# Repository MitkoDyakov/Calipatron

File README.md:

# Calipatorn
I design my own digital caliper based on STM32F103C8T6 blue pill.

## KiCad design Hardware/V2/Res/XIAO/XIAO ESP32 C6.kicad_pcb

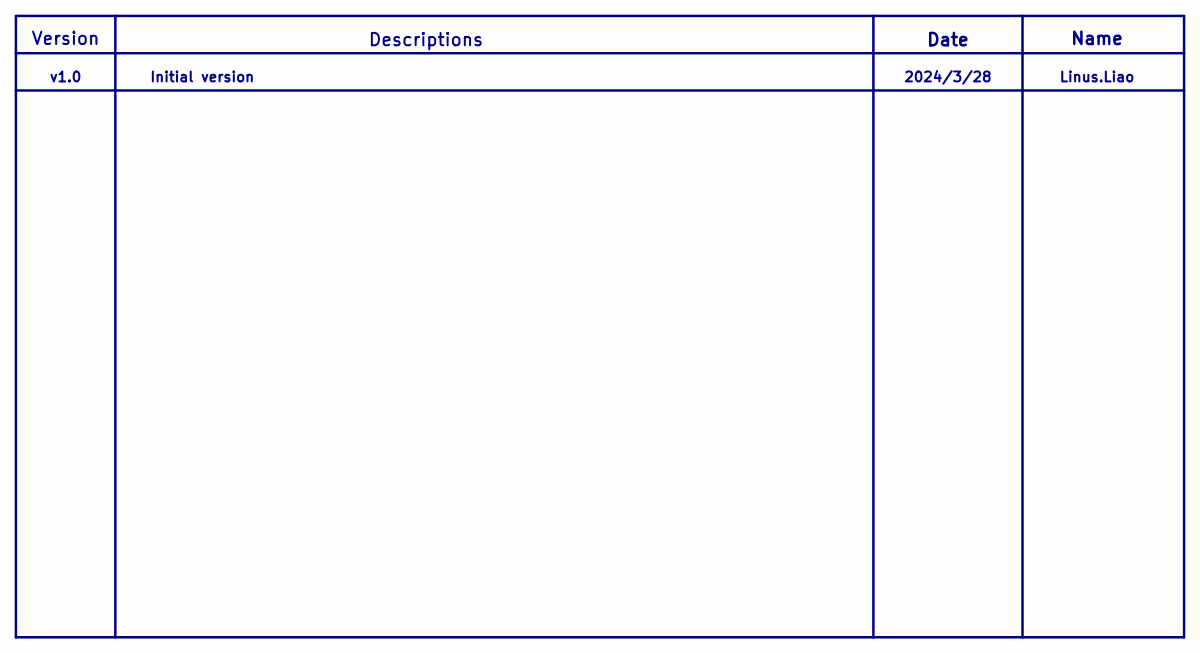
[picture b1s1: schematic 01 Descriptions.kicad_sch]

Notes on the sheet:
Date
Descriptions
Linus.Liao
2024/3/28
v1.0
Initial version
Name
Version

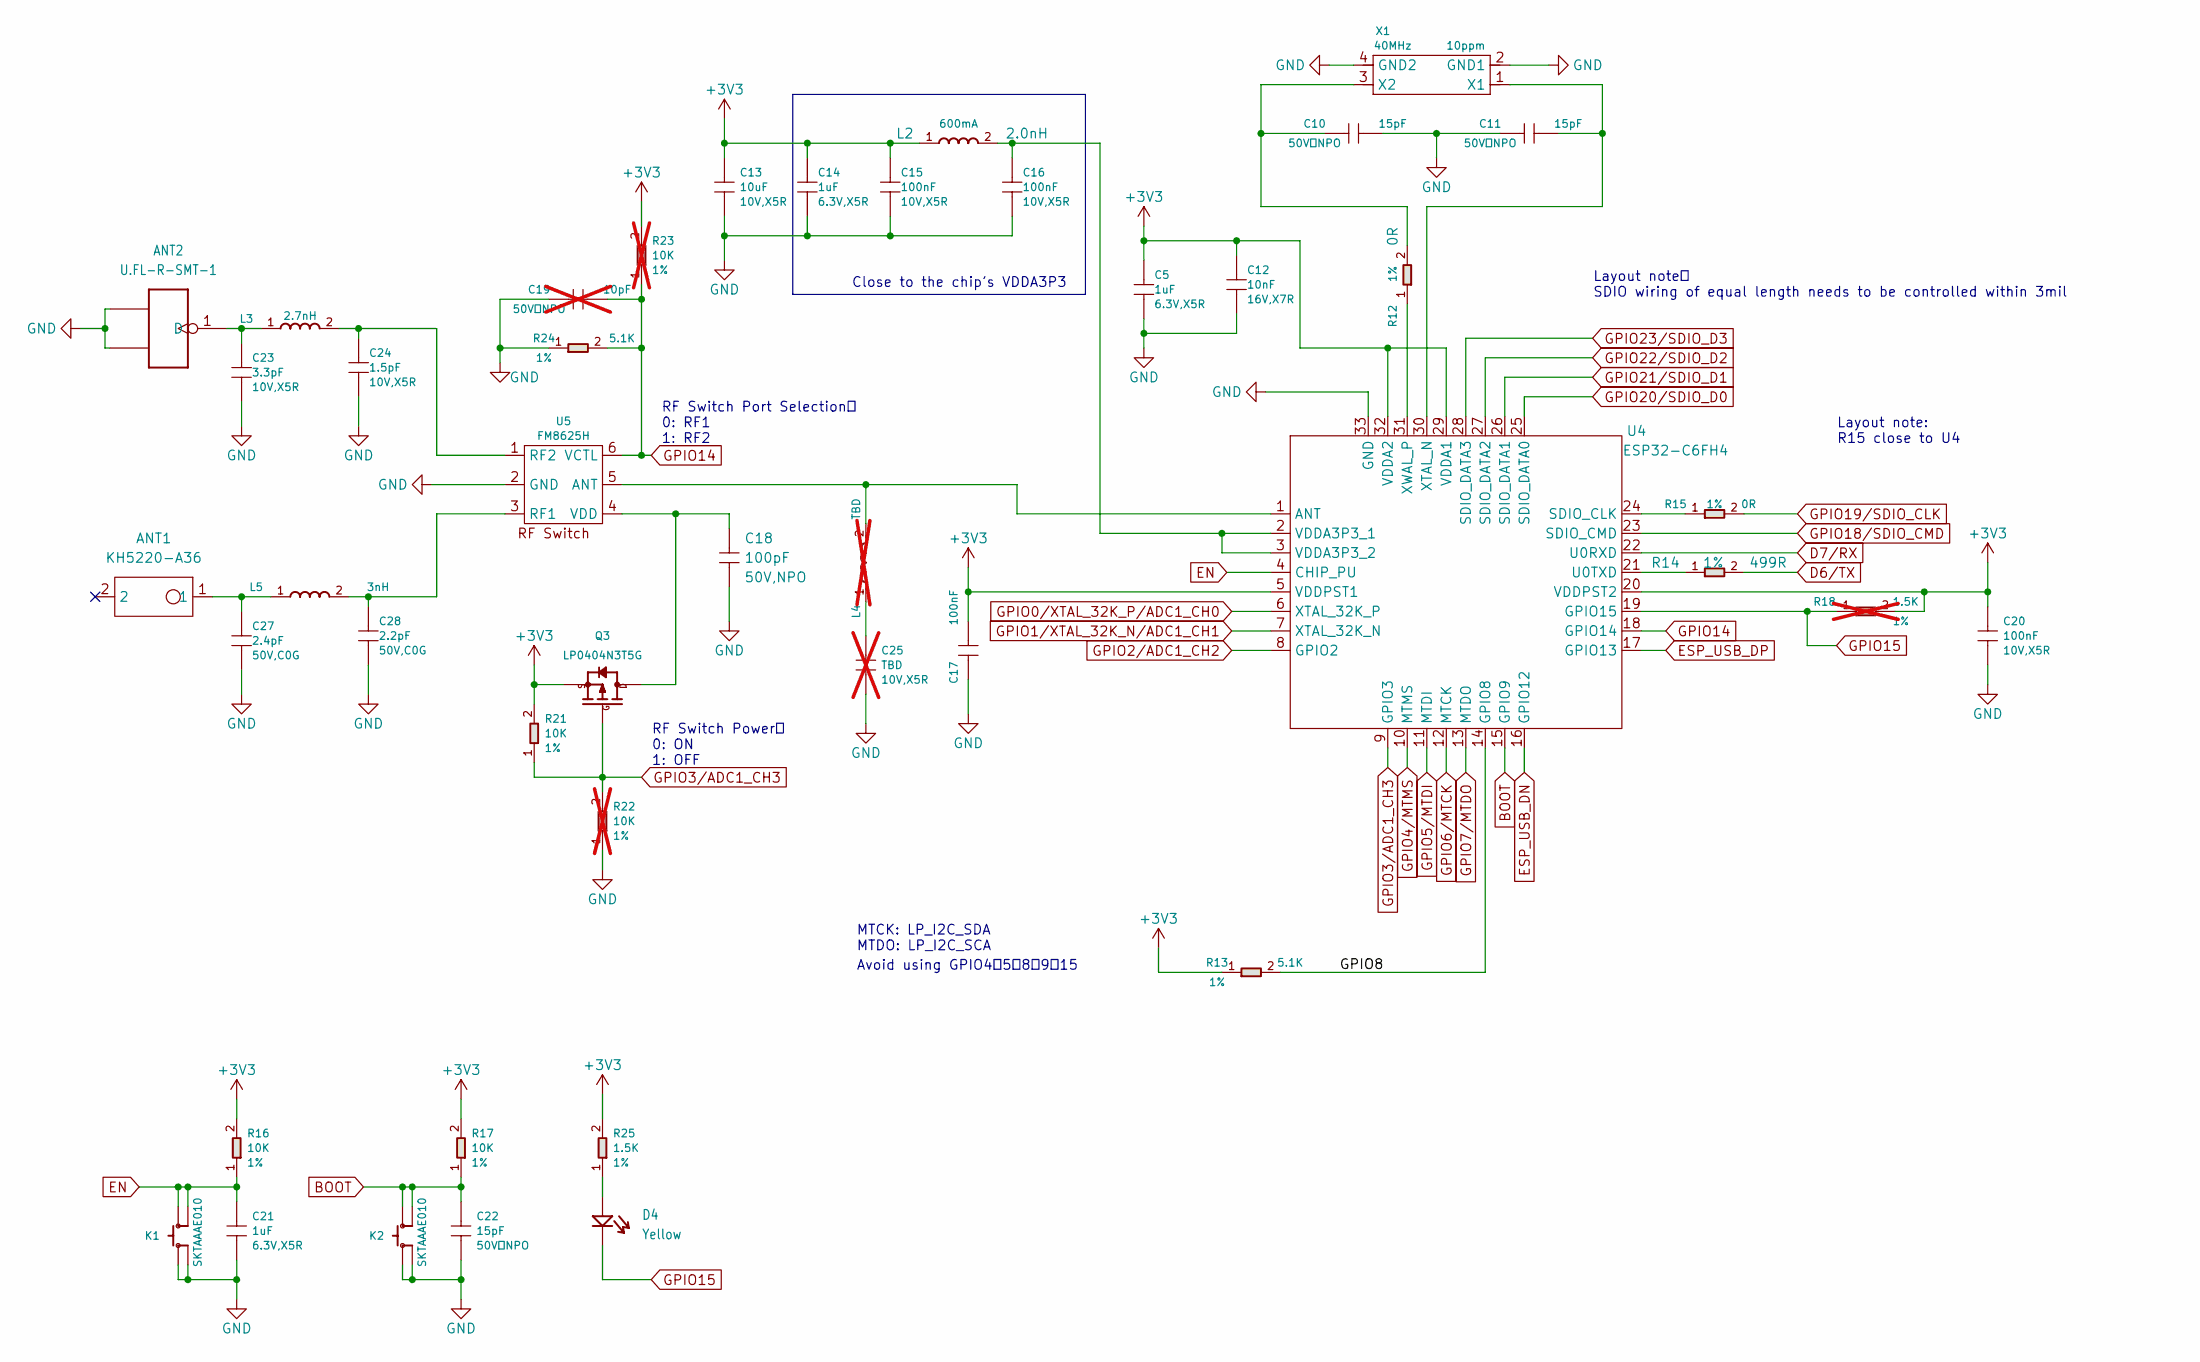
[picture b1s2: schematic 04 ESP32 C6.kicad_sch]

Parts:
ANT1: KH5220-A36; ANT2P-5.2x2x1.1MM; MPN KH5220-A36
ANT2: U.FL-R-SMT-1; U-FL3P-SMD-2.6X2.6X1.0MM; MPN U.FL-R-SMT-1
C5, C14, C21: 1uF; C0201; Voltage Rating 6.3V,X5R; MPN CC0201MRX5R5BB105
C10, C11, C22: 15pF; C0201; Voltage Rating 50V，NPO; MPN CC0201JRNPO9BN150
C12: 10nF; C0201; Voltage Rating 16V,X7R; MPN CC0201KRX7R7BB103
C13: 10uF; C0402; Voltage Rating 10V,X5R; MPN CC0402MRX5R6BB106
C15, C16, C17, C20: 100nF; C0201; Voltage Rating 10V,X5R; MPN CC0201KRX5R6BB104
C18: 100pF; C0201; Voltage Rating 50V,NPO; MPN CC0201JRNPO9BN101
C19: 10pF; C0201; Voltage Rating 50V，NPO; MPN CC0201JRNPO8BN100; not fitted
C23: 3.3pF; C0201; Voltage Rating 10V,X5R; MPN CQ0201BRNPO8BN3R3
C24: 1.5pF; C0201; Voltage Rating 10V,X5R; MPN CC0201BRNPO9BN1R5
C25: TBD; C0201; Voltage Rating 10V,X5R; Part Type Ceramic; not fitted
C27: 2.4pF; C0201; Voltage Rating 50V,C0G; MPN GRM0335C1H2R4BA01D
C28: 2.2pF; C0201; Voltage Rating 50V,C0G; MPN GRM0335C1H2R2BA01D
D4: Yellow; LED-0402; MPN 16-213/Y2C-AN2Q1B/3T
K1, K2: SKTAAAE010; SW4-SMD-2.8-2.6X1.6X0.53MM; MPN SKTAAAE010
L2: 2.0nH; L0201; Rating 600mA; MPN LQP03HQ2N0B02D
L3: 2.7nH; L0201; MPN LQP03TN2N7B02D
L4: TBD; L0201; Part Type L; not fitted
L5: 3nH; L0201; MPN LQP03TN3N0B02D
Q3: LP0404N3T5G; PMOS_1.0X0.6X0.35MM; MPN LP0404N3T5G
R12, R15: 0R; R0201; Power Rating 1%; MPN RC0201FR-070RL
R13, R24: 5.1K; R0201; Power Rating 1%; MPN RC0201FR-075K1L
R14: 499R; R0201; Power Rating 1%; MPN RC0201FR-07499RL
R16, R17, R21: 10K; R0201; Power Rating 1%; MPN RC0201FR-0710KL
R18: 1.5K; R0201; Power Rating 1%; MPN RC0201FR-071K5L; not fitted
R22, R23: 10K; R0201; Power Rating 1%; MPN RC0201FR-0710KL; not fitted
R25: 1.5K; R0201; Power Rating 1%; MPN RC0201FR-071K5L
U4: ESP32-C6FH4; QFN32-0.5-5X5MM; MPN ESP32-C6FH4
U5: FM8625H; DFN6-0.4-1.1X0.7X0.45MM; MPN FM8625H
X1: 40MHz; X4-SMD-1.6X1.2MM; Rating 10ppm; MPN CJ17-400001010B20

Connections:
+3V3: C5.1, C12.1, C13.1, C14.1, C15.1, C17.1, C20.1, L2.1, Q3.2 (S), R13.1, R16.2, R17.2, R18.2, R21.2, R23.2, R25.2, U4.5 (VDDPST1), U4.20 (VDDPST2), U4.29 (VDDA1), U4.32 (VDDA2); also elsewhere on the board
/04 ESP32 C6/GPIO8: R13.2, U4.14 (GPIO8)
BOOT: C22.1, K2.3 (B0), K2.4 (B1), R17.1, U4.15 (GPIO9); also elsewhere on the board
D6/TX: R14.2; also elsewhere on the board
D7/RX: U4.22 (U0RXD); also elsewhere on the board
EN: C21.1, K1.3 (B0), K1.4 (B1), R16.1, U4.4 (CHIP_PU); also elsewhere on the board
ESP_USB_DN: U4.16 (GPIO12); also elsewhere on the board
ESP_USB_DP: U4.17 (GPIO13); also elsewhere on the board
GND: ANT2.2 (GND1), ANT2.3 (GND2), C5.2, C10.2, C11.1, C12.2, C13.2, C14.2, C15.2, C16.2, C17.2, C18.2, C19.1, C20.2, C21.2, C22.2, C23.2, C24.2, C25.2, C27.2, C28.2, K1.1 (A0), K1.2 (A1), K2.1 (A0), K2.2 (A1), R22.1, R24.1, U4.33 (GND), U5.2 (GND), X1.2 (GND1), X1.4 (GND2); also elsewhere on the board
GPIO0/XTAL_32K_P/ADC1_CH0: U4.6 (XTAL_32K_P); also elsewhere on the board
GPIO1/XTAL_32K_N/ADC1_CH1: U4.7 (XTAL_32K_N); also elsewhere on the board
GPIO2/ADC1_CH2: U4.8 (GPIO2); also elsewhere on the board
GPIO3/ADC1_CH3: Q3.1 (G), R21.1, R22.2, U4.9 (GPIO3)
GPIO4/MTMS: U4.10 (MTMS); also elsewhere on the board
GPIO5/MTDI: U4.11 (MTDI); also elsewhere on the board
GPIO6/MTCK: U4.12 (MTCK); also elsewhere on the board
GPIO7/MTDO: U4.13 (MTDO); also elsewhere on the board
GPIO14: C19.2, R23.1, R24.2, U4.18 (GPIO14), U5.6 (VCTL)
GPIO15: D4.2 (-), R18.1, U4.19 (GPIO15)
GPIO18/SDIO_CMD: U4.23 (SDIO_CMD); also elsewhere on the board
GPIO19/SDIO_CLK: R15.2; also elsewhere on the board
GPIO20/SDIO_D0: U4.25 (SDIO_DATA0); also elsewhere on the board
GPIO21/SDIO_D1: U4.26 (SDIO_DATA1); also elsewhere on the board
GPIO22/SDIO_D2: U4.27 (SDIO_DATA2); also elsewhere on the board
GPIO23/SDIO_D3: U4.28 (SDIO_DATA3); also elsewhere on the board
unnamed: ANT1.1, C27.1, L5.1
unnamed: ANT2.1 (D), C23.1, L3.1
unnamed: C25.1, L4.1
unnamed: D4.1 (+), R25.1
unnamed: C18.1, Q3.3 (D), U5.4 (VDD)
unnamed: L4.2, U4.1 (ANT), U5.5 (ANT)
unnamed: R15.1, U4.24 (SDIO_CLK)
unnamed: R14.1, U4.21 (U0TXD)
unnamed: C16.1, L2.2, U4.2 (VDDA3P3_1), U4.3 (VDDA3P3_2)
unnamed: C11.2, U4.30 (XTAL_N), X1.1 (X1)
unnamed: R12.1, U4.31 (XWAL_P)
unnamed: C28.1, L5.2, U5.3 (RF1)
unnamed: C24.1, L3.2, U5.1 (RF2)
unnamed: C10.1, R12.2, X1.3 (X2)

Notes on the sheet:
Avoid using GPIO4、5、8、9、15
RF Switch Power： 0: ON 1: OFF
Layout note: R15 close to U4
Close to the chip's VDDA3P3
Layout note： SDIO wiring of equal length needs to be controlled within 3mil
RF Switch Port Selection： 0: RF1 1: RF2
MTCK: LP_I2C_SDA MTDO: LP_I2C_SCA

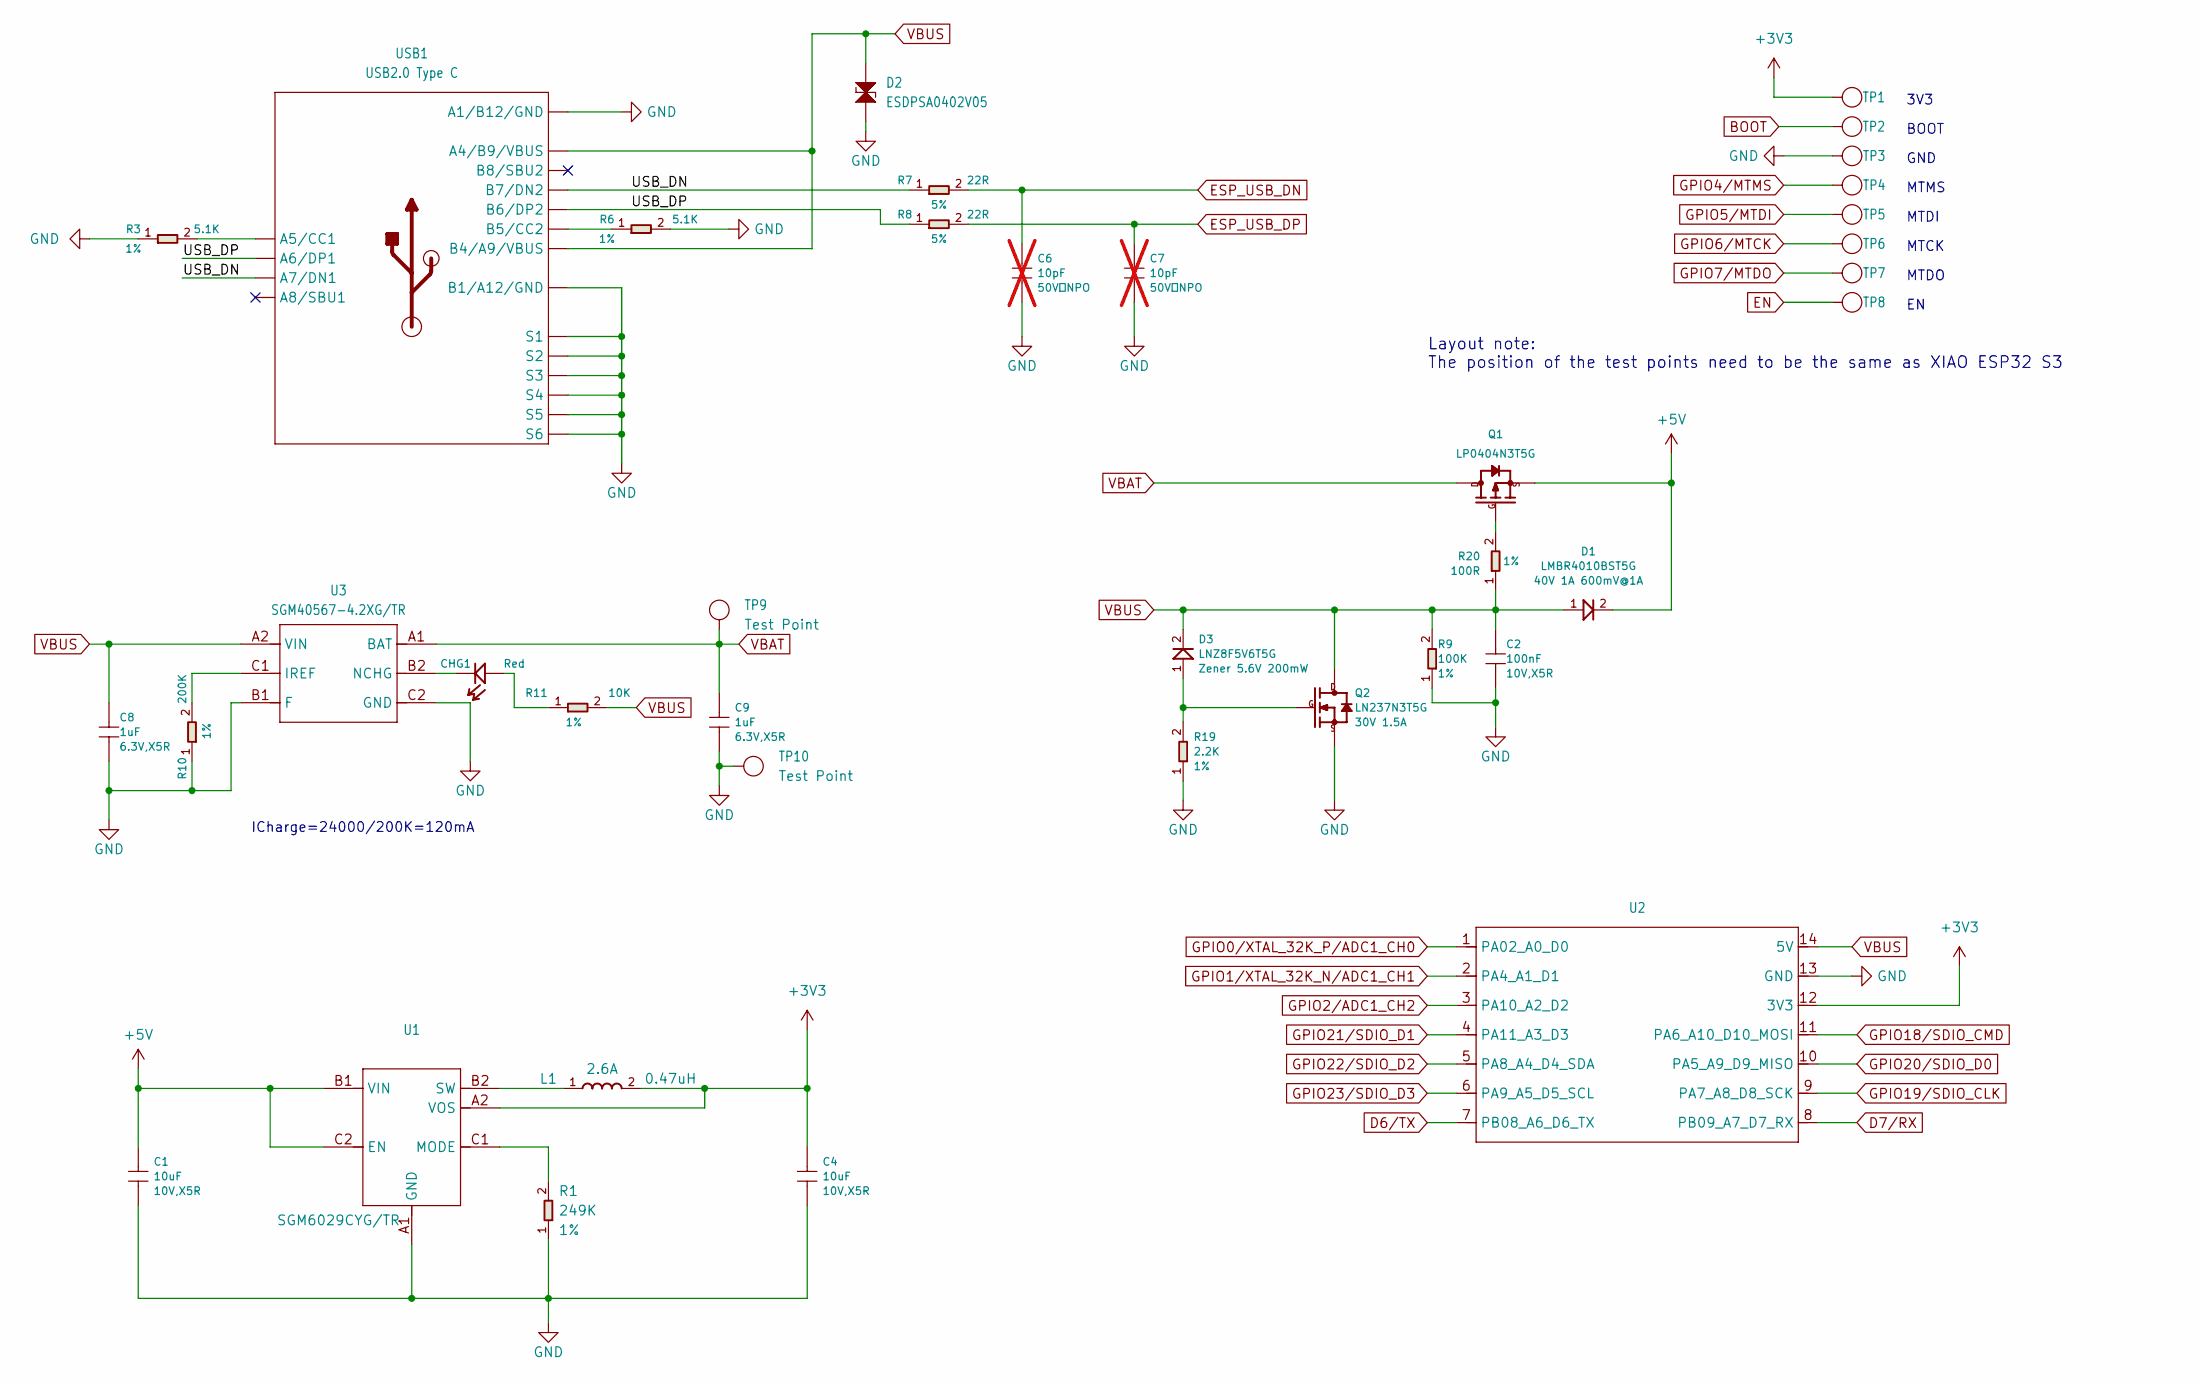
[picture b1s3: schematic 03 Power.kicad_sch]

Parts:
C1, C4: 10uF; C0402; Voltage Rating 10V,X5R; MPN CC0402MRX5R6BB106
C2: 100nF; C0201; Voltage Rating 10V,X5R; MPN CC0201KRX5R6BB104
C6, C7: 10pF; C0201; Voltage Rating 50V，NPO; MPN CC0201JRNPO8BN100; not fitted
C8, C9: 1uF; C0201; Voltage Rating 6.3V,X5R; MPN CC0201MRX5R5BB105
CHG1: Red; LED-0402; MPN BL-HUB37A-AV-TRB
D1: LMBR4010BST5G; DFN1006-2L; Rating 40V 1A 600mV@1A; MPN LMBR4010BST5G
D2: ESDPSA0402V05; ESD-0402; MPN ESDPSA0402V05
D3: LNZ8F5V6T5G; DFN1006-2L; Rating Zener 5.6V 200mW; MPN LNZ8F5V6T5G
L1: 0.47uH; L0603; Rating 2.6A; MPN TFM160808ALC-R47MTAA
Q1: LP0404N3T5G; PMOS_1.0X0.6X0.35MM; MPN LP0404N3T5G
Q2: LN237N3T5G; PMOS_1.0X0.6X0.35MM; Rating 30V 1.5A; MPN LN237N3T5G
R1: 249K; R0201; Power Rating 1%; MPN RC0201FR-07249KL
R3, R6: 5.1K; R0201; Power Rating 1%; MPN RC0201FR-075K1L
R7, R8: 22R; R0201; Power Rating 5%; MPN RC0201JR-0722RL
R9: 100K; R0201; Power Rating 1%; MPN RC0201FR-07100KL
R10: 200K; R0201; Power Rating 1%; MPN RC0201FR-07200KL
R11: 10K; R0201; Power Rating 1%; MPN RC0201FR-0710KL
R19: 2.2K; R0201; Power Rating 1%; MPN RC0201FR-072K2L
R20: 100R; R0201; Power Rating 1%; MPN RC0201FR-07100RL
TP1, TP2, TP3, TP4, TP5, TP6, TP7, TP8: Test Point; TP-D45MIL; Part Type Test Point
TP9, TP10: Test Point; TP-80X40MIL; Part Type Test Point
U1: SMD IC PMIC;DCDC Buck-ADJ-1A,Vin 1.95V to 5.5V,Vo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; BGA6-0.35-0.745X10.95X0.4MM; MPN SGM6029CYG/TR
U2: MOUDLE14P-XIAO-HALF-HOLE
U3: SGM40567-4.2XG/TR; WLCSP-0.4-0.92X1.16X0.4MM; MPN SGM40567-4.2XG/TR
USB1: USB2.0 Type C; USB2.0-TYPE-C; MPN UBF31-0171

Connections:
+3V3: C4.1, L1.2, TP1.1 (T), U1.A2 (VOS), U2.12 (3V3); also elsewhere on the board
+5V: C1.1, D1.2, Q1.2 (S), U1.B1 (VIN), U1.C2 (EN)
/03 Power/USB_DN: R7.1, USB1.A7 (A7/DN1), USB1.B7 (B7/DN2)
/03 Power/USB_DP: R8.1, USB1.A6 (A6/DP1), USB1.B6 (B6/DP2)
BOOT: TP2.1 (T); also elsewhere on the board
D6/TX: U2.7 (PB08_A6_D6_TX); also elsewhere on the board
D7/RX: U2.8 (PB09_A7_D7_RX); also elsewhere on the board
EN: TP8.1 (T); also elsewhere on the board
ESP_USB_DN: C6.1, R7.2; also elsewhere on the board
ESP_USB_DP: C7.1, R8.2; also elsewhere on the board
GND: C1.2, C2.2, C4.2, C6.2, C7.2, C8.2, C9.2, D2.1, Q2.2 (S), R1.1, R3.1, R6.2, R9.1, R10.1, R19.1, TP3.1 (T), TP10.1 (T), U1.A1 (GND), U2.13 (GND), U3.B1 (F), U3.C2 (GND), USB1.A1_B12 (A1/B12/GND), USB1.B1_A12 (B1/A12/GND), USB1.S1, USB1.S2, USB1.S3, USB1.S4, USB1.S5, USB1.S6; also elsewhere on the board
GPIO0/XTAL_32K_P/ADC1_CH0: U2.1 (PA02_A0_D0); also elsewhere on the board
GPIO1/XTAL_32K_N/ADC1_CH1: U2.2 (PA4_A1_D1); also elsewhere on the board
GPIO2/ADC1_CH2: U2.3 (PA10_A2_D2); also elsewhere on the board
GPIO4/MTMS: TP4.1 (T); also elsewhere on the board
GPIO5/MTDI: TP5.1 (T); also elsewhere on the board
GPIO6/MTCK: TP6.1 (T); also elsewhere on the board
GPIO7/MTDO: TP7.1 (T); also elsewhere on the board
GPIO18/SDIO_CMD: U2.11 (PA6_A10_D10_MOSI); also elsewhere on the board
GPIO19/SDIO_CLK: U2.9 (PA7_A8_D8_SCK); also elsewhere on the board
GPIO20/SDIO_D0: U2.10 (PA5_A9_D9_MISO); also elsewhere on the board
GPIO21/SDIO_D1: U2.4 (PA11_A3_D3); also elsewhere on the board
GPIO22/SDIO_D2: U2.5 (PA8_A4_D4_SDA); also elsewhere on the board
GPIO23/SDIO_D3: U2.6 (PA9_A5_D5_SCL); also elsewhere on the board
unnamed: CHG1.1 (+), R11.1
unnamed: CHG1.2 (-), U3.B2 (NCHG)
unnamed: Q1.1 (G), R20.2
unnamed: D3.1, Q2.1 (G), R19.2
unnamed: R1.2, U1.C1 (MODE)
unnamed: L1.1, U1.B2 (SW)
unnamed: R10.2, U3.C1 (IREF)
unnamed: R3.2, USB1.A5 (A5/CC1)
unnamed: R6.1, USB1.B5 (B5/CC2)
VBAT: C9.1, Q1.3 (D), TP9.1 (T), U3.A1 (BAT)
VBUS: C2.1, C8.1, D1.1, D2.2, D3.2, Q2.3 (D), R9.2, R11.2, R20.1, U2.14 (5V), U3.A2 (VIN), USB1.A4_B9 (A4/B9/VBUS), USB1.B4_A9 (B4/A9/VBUS)

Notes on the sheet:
MTMS
MTDI
ICharge=24000/200K=120mA
GND
MTDO
Layout note: The position of the test points need to be the same as XIAO ESP32 S3
MTCK
BOOT
3V3

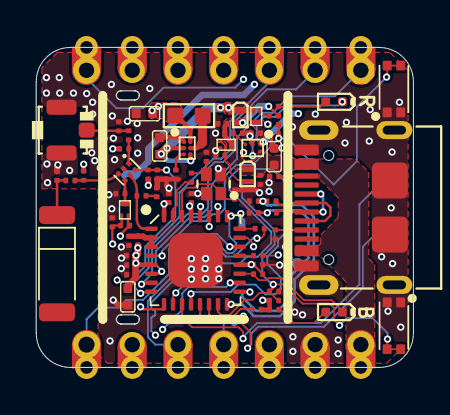
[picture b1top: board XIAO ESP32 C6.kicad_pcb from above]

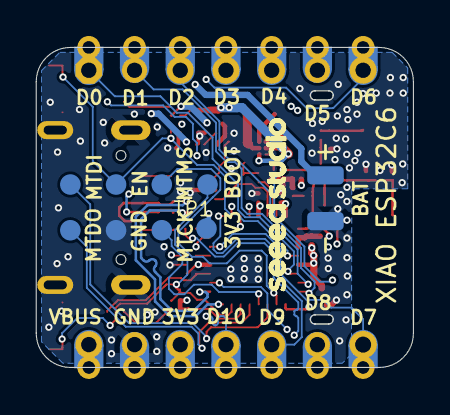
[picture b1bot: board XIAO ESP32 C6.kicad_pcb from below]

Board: 4 copper layers, 21.0 x 17.8 mm, 82 parts (10 on the bottom side), 53 nets.

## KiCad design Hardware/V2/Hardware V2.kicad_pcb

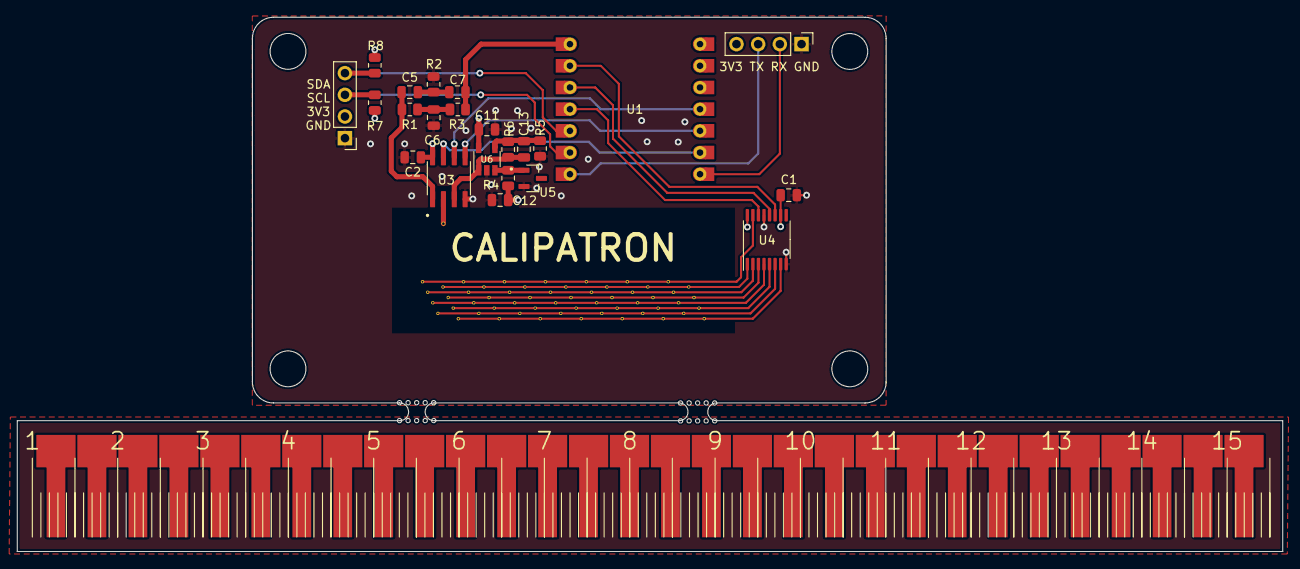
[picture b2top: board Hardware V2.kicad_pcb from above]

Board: 4 copper layers, 148.3 x 62.6 mm, 24 parts (1 on the bottom side), 28 nets.

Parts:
C1, C2, C11, C12: 100nF; C_0805_2012Metric
C5, C7: 33nF; C_0805_2012Metric
C6: 47nF; C_0805_2012Metric
C13: NP; C_0805_2012Metric
J1, J2: Conn_01x04; PinHeader_1x04_P2.54mm_Vertical
R1, R3, R7, R8: 100K; R_0805_2012Metric
R2: 33K; R_0805_2012Metric
R4: 160R; R_0805_2012Metric
R5: 10K; R_0805_2012Metric
R6: 5K; R_0805_2012Metric
U1: XIAO; Mod
U2: signal_generator; excitation_electrodes
U3: MCP6S21-I_SN; SOIC127P600X175-8N
U4: 74HC595; TSSOP-16_4.4x5mm_P0.65mm
U5: ADR510ARTZ-REEL7; SOT95P237X112-3N
U6: AD8603; TSOT-23-5

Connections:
3V3: C1.2, C2.2, C11.2, C12.2, J1.2, J2.4, R4.1, R7.1, R8.1, U1.12, U3.8, U4.10, U4.16, U6.5
A+: U2.8, U4.15
A-: U2.4, U4.1
B+: U2.7, U4.2
B-: U2.3, U4.3
C+: U2.6, U4.4
C-: U2.2, U4.5
CS: U1.10, U3.5
D+: U2.5, U4.6
D-: U2.1, U4.7
GND: C1.1, C2.1, C6.2, C11.1, C12.1, J1.1, J2.1, R2.2, R5.2, U1.13, U3.4, U4.8, U4.13, U5.2, U6.2
unnamed: C5.1, C7.2, R2.1
unnamed: C5.2, R1.2, U3.1
unnamed: C6.1, R1.1, R3.2
unnamed: C13.2, R5.1, R6.2, U6.4
unnamed: R4.2, U5.1, U6.3
RCLK: U1.3, U4.12
RX: J2.2, U1.8
SCK: U1.9, U3.7
SCL: J1.3, R7.2, U1.6
SDA: J1.4, R8.2, U1.5
SENSE: U2.9, U3.2
SER: U1.4, U4.14
SI: U1.11, U3.6
SIGNAL: C7.1, R3.1, U1.1
SRCLK: U1.2, U4.11
TX: J2.3, U1.7
Vref: C13.1, R6.1, U3.3, U6.1

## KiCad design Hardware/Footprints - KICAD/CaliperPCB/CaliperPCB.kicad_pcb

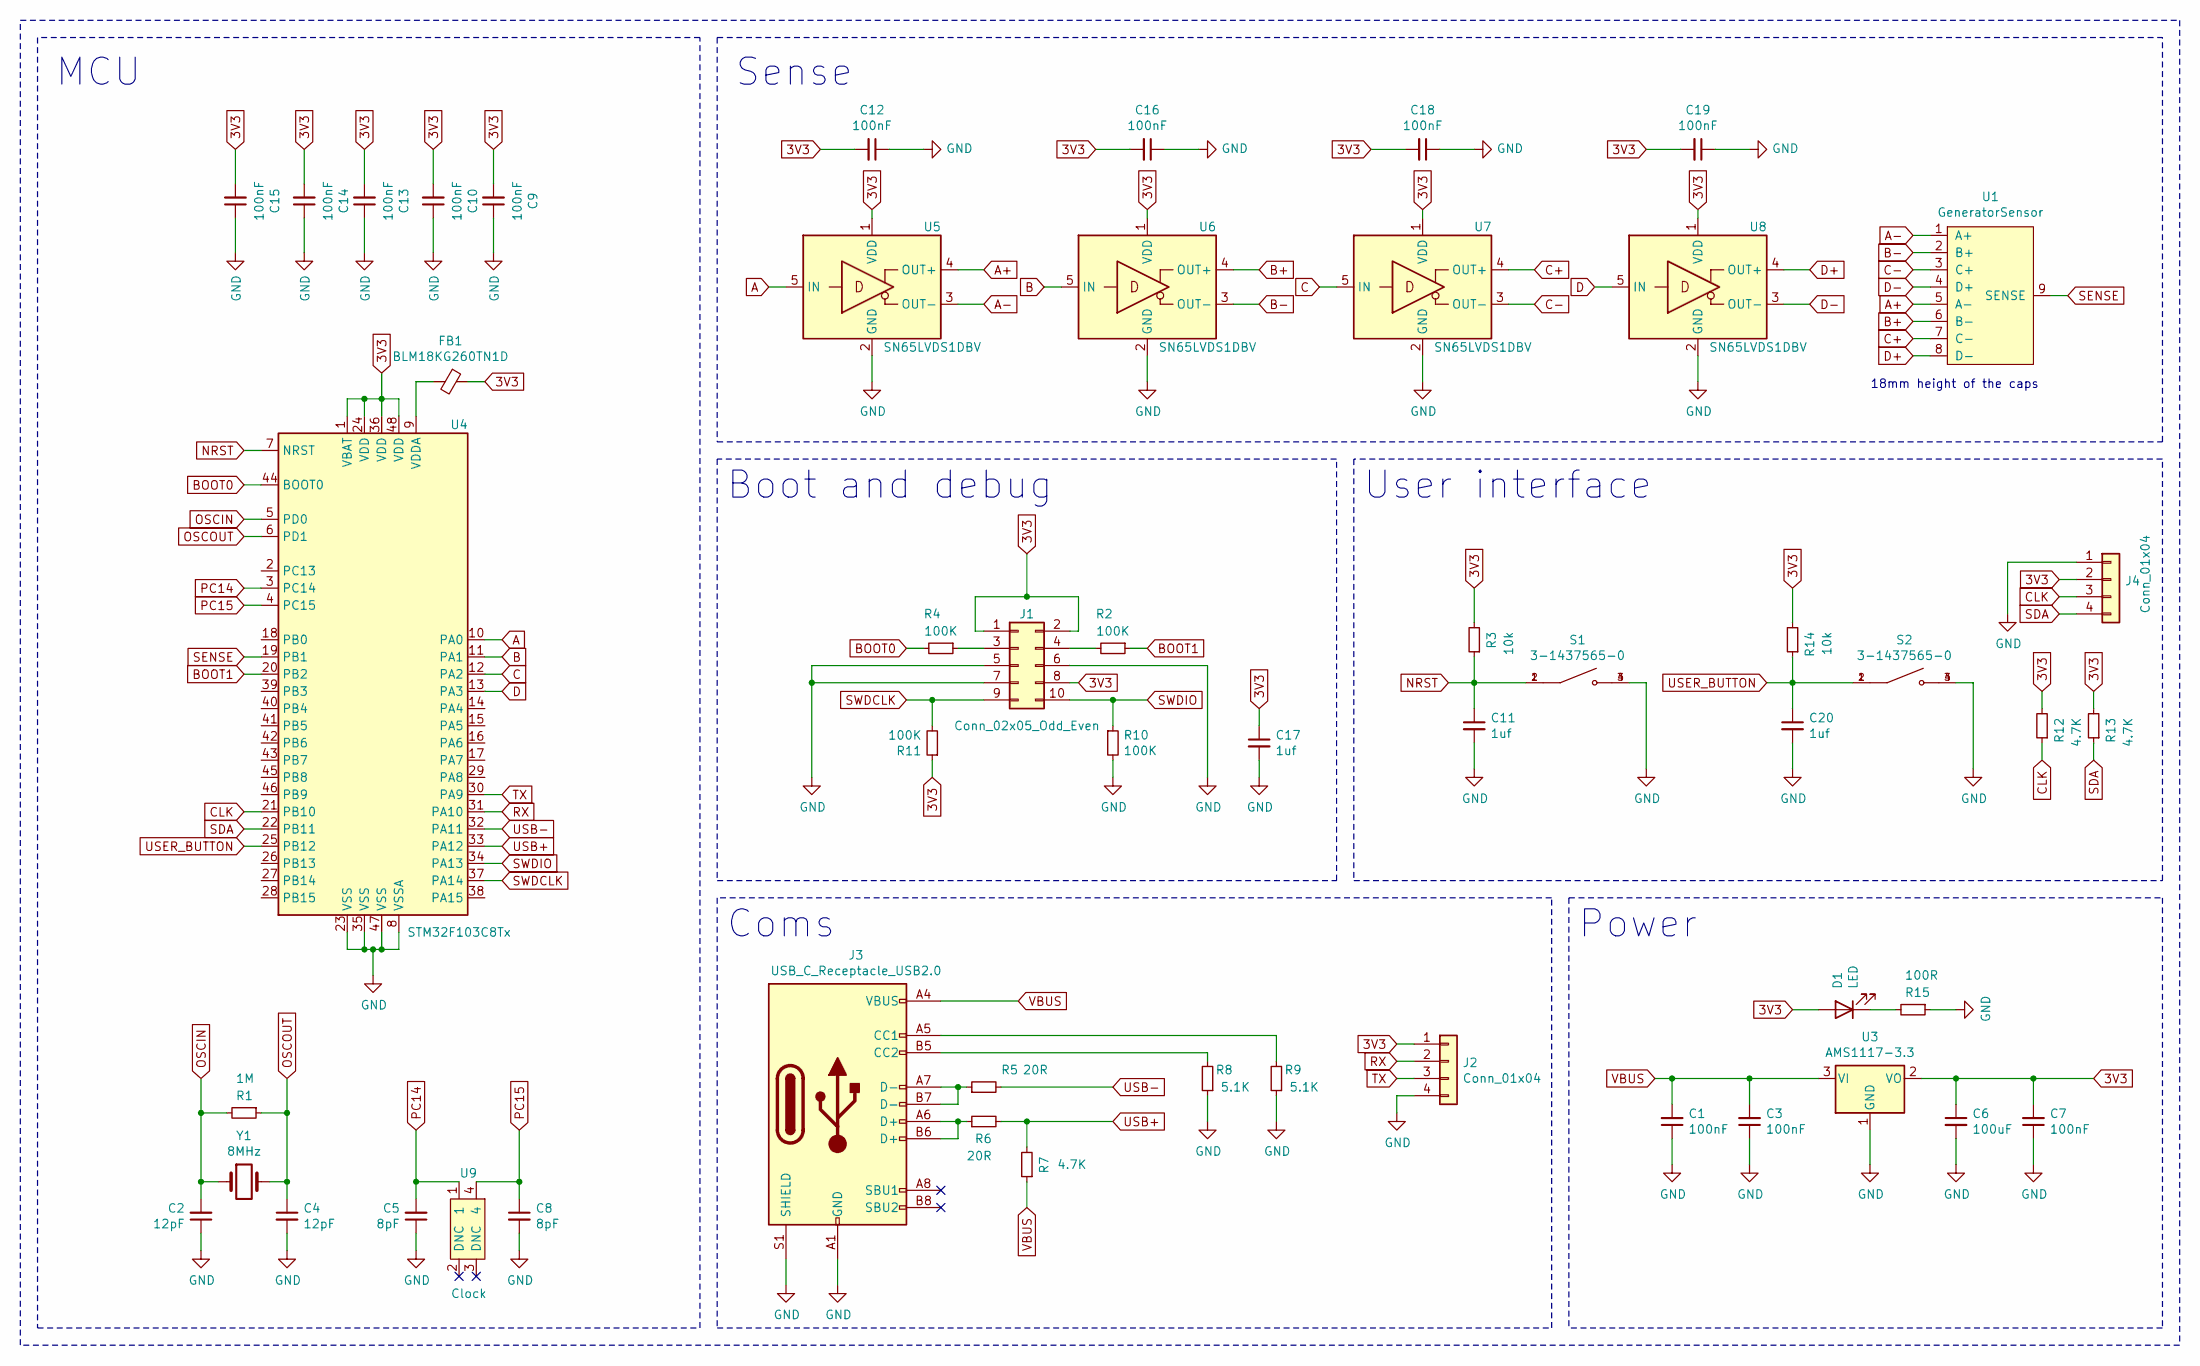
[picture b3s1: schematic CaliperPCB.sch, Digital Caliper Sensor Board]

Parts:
C1, C3, C7, C9, C10, C12, C13, C14, C15, C16, C18, C19: 100nF; C_0603_1608Metric
C2, C4: 12pF; C_0603_1608Metric
C5, C8: 8pF; C_0603_1608Metric
C6: 100uF; C_0603_1608Metric
C11, C17, C20: 1uf; C_0603_1608Metric
D1: LED; LED_0603_1608Metric
FB1: BLM18KG260TN1D; C_0603_1608Metric
J1: Conn_02x05_Odd_Even; PinHeader_2x05_P2.54mm_Vertical
J2, J4: Conn_01x04; PinSocket_1x04_P2.54mm_Vertical
J3: USB_C_Receptacle_USB2.0; USB_C_Receptacle_HRO_TYPE-C-31-M-12
R1: 1M; R_0603_1608Metric
R2, R4, R10, R11: 100K; R_0603_1608Metric
R3, R14: 10k; R_0603_1608Metric
R5, R6: 20R; R_0603_1608Metric
R7, R12, R13: 4.7K; R_0603_1608Metric
R8, R9: 5.1K; R_0603_1608Metric
R15: 100R; R_0603_1608Metric
S1, S2: 3-1437565-0; SW_3-1437565-0
U1: GeneratorSensor; excitation_electrodes
U3: AMS1117-3.3; SOT-223-3_TabPin2
U4: STM32F103C8Tx; LQFP-48_7x7mm_P0.5mm
U5, U6, U7, U8: SN65LVDS1DBV; SOT-23-5
U9: Clock; XTAL_MC-306_32.7680K-A__ROHS
Y1: 8MHz; Crystal_SMD_5032-2Pin_5.0x3.2mm

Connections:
3V3: C6.1, C7.2, C9.2, C10.2, C12.2, C13.2, C14.2, C15.2, C16.2, C17.1, C18.2, C19.2, D1.2 (A), FB1.1, J1.1, J1.2, J1.8, J2.1, J4.2, R3.2, R11.1, R12.2, R13.2, R14.2, U3.2 (VO), U4.1 (VBAT), U4.24 (VDD), U4.36 (VDD), U4.48 (VDD), U5.1 (VDD), U6.1 (VDD), U7.1 (VDD), U8.1 (VDD)
A: U4.10 (PA0), U5.5 (IN)
A+: U1.5 (A-), U5.4 (OUT+)
A-: U1.1 (A+), U5.3 (OUT-)
B: U4.11 (PA1), U6.5 (IN)
B+: U1.6 (B-), U6.4 (OUT+)
B-: U1.2 (B+), U6.3 (OUT-)
BOOT0: R4.2, U4.44 (BOOT0)
BOOT1: R2.1, U4.20 (PB2)
C: U4.12 (PA2), U7.5 (IN)
C+: U1.7 (C-), U7.4 (OUT+)
C-: U1.3 (C+), U7.3 (OUT-)
CLK: J4.3, R12.1, U4.21 (PB10)
D: U4.13 (PA3), U8.5 (IN)
D+: U1.8 (D-), U8.4 (OUT+)
D-: U1.4 (D+), U8.3 (OUT-)
GND: C1.1, C2.1, C3.1, C4.2, C5.1, C6.2, C7.1, C8.2, C9.1, C10.1, C11.2, C12.1, C13.1, C14.1, C15.1, C16.1, C17.2, C18.1, C19.1, C20.2, J1.5, J1.6, J1.7, J2.4, J3.A1 (GND), J3.A12 (GND), J3.B1 (GND), J3.B12 (GND), J3.S1 (SHIELD), J4.1, R8.1, R9.1, R10.2, R15.1, S1.3, S1.4, S2.3, S2.4, U3.1 (GND), U4.8 (VSSA), U4.23 (VSS), U4.35 (VSS), U4.47 (VSS), U5.2 (GND), U6.2 (GND), U7.2 (GND), U8.2 (GND)
NRST: C11.1, R3.1, S1.1, S1.2, U4.7 (NRST)
unnamed: D1.1 (K), R15.2
unnamed: FB1.2, U4.9 (VDDA)
unnamed: J1.3, R4.1
unnamed: J1.4, R2.2
unnamed: J3.A5 (CC1), R9.2
unnamed: J3.A6 (D+), J3.B6 (D+), R6.1
unnamed: J3.A7 (D-), J3.B7 (D-), R5.1
unnamed: J3.B5 (CC2), R8.2
OSCIN: C2.2, R1.2, U4.5 (PD0), Y1.1
OSCOUT: C4.1, R1.1, U4.6 (PD1), Y1.2
PC14: C5.2, U4.3 (PC14), U9.1
PC15: C8.1, U4.4 (PC15), U9.4
RX: J2.2, U4.31 (PA10)
SDA: J4.4, R13.1, U4.22 (PB11)
SEMSE: U1.9 (SENSE), U4.19 (PB1)
SWDCLK: J1.9, R11.2, U4.37 (PA14)
SWDIO: J1.10, R10.1, U4.34 (PA13)
TX: J2.3, U4.30 (PA9)
USB+: R6.2, R7.2, U4.33 (PA12)
USB-: R5.2, U4.32 (PA11)
USER_BUTTON: C20.1, R14.1, S2.1, S2.2, U4.25 (PB12)
VBUS: C1.2, C3.2, J3.A4 (VBUS), J3.A9 (VBUS), J3.B4 (VBUS), J3.B9 (VBUS), R7.1, U3.3 (VI)

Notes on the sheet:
18mm height of the caps
MCU
Sense
Boot and debug
User interface
Power
Coms

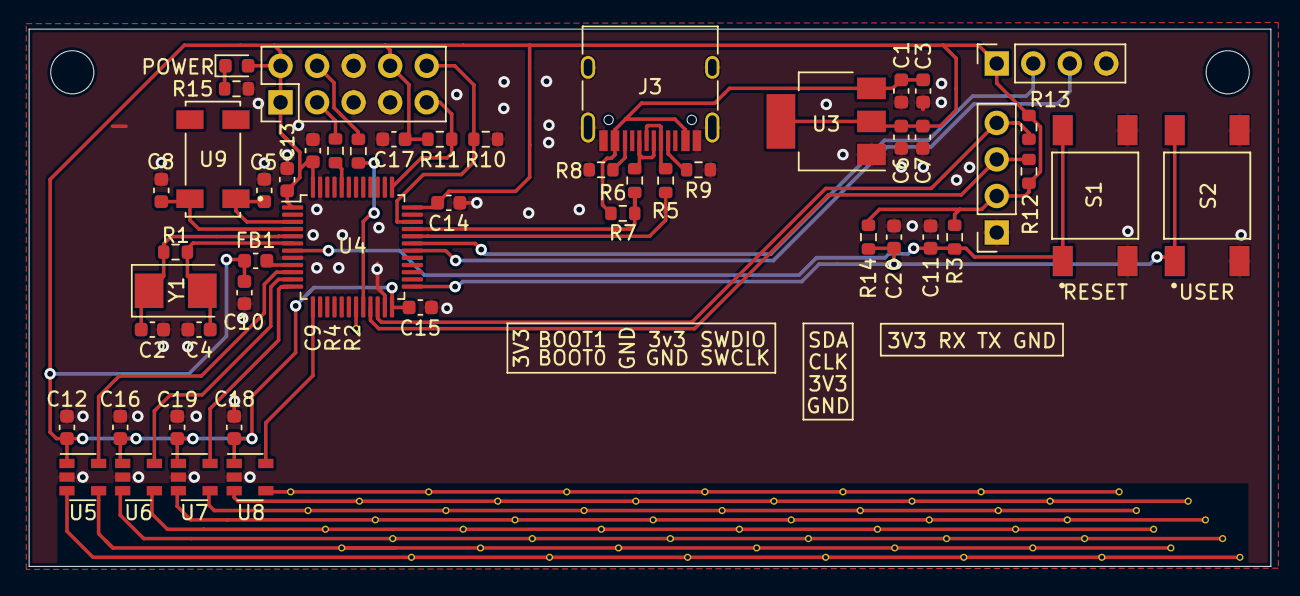
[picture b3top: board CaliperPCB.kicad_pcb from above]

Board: 2 copper layers, 86.3 x 37.4 mm, 52 parts (1 on the bottom side), 40 nets.

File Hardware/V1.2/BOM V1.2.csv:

"Source:","D:\Projects\DigitalCaliper\CaliperPCB\CaliperPCB.sch"
"Date:","9/15/2024 2:43:23 PM"
"Tool:","Eeschema (5.1.12)-1"
"Generator:","C:\Program Files\KiCad\bin\scripting\plugins/bom_csv_grouped_by_value_with_fp.py"
"Component Count:","65"
"Ref","Qnty","Value","Cmp name","Footprint","Description","Vendor"
"C1, C3, C7, C9, C10, C12, C13, C14, C15, C17, C21, C22, ","12","100nF","C_Small","Capacitor_SMD:C_0603_1608Metric","Unpolarized capacitor, small symbol",""
"C2, C4, ","2","12pF","C_Small","Capacitor_SMD:C_0603_1608Metric","Unpolarized capacitor, small symbol",""
"C5, C8, ","2","8pF","C_Small","Capacitor_SMD:C_0603_1608Metric","Unpolarized capacitor, small symbol",""
"C6, ","1","10uF","C_Small","Capacitor_SMD:C_0603_1608Metric","Unpolarized capacitor, small symbol",""
"C11, C20, ","2","1uf","C_Small","Capacitor_SMD:C_0603_1608Metric","Unpolarized capacitor, small symbol",""
"C16, C19, ","2","33nF","C_Small","Capacitor_SMD:C_0603_1608Metric","Unpolarized capacitor, small symbol",""
"C18, ","1","47nF","C_Small","Capacitor_SMD:C_0603_1608Metric","Unpolarized capacitor, small symbol",""
"C23, ","1","NP","C_Small","Capacitor_SMD:C_0603_1608Metric","Unpolarized capacitor, small symbol",""
"D1, ","1","POWER","LED","LED_SMD:LED_0603_1608Metric","Light emitting diode",""
"FB1, ","1","0R / BLM18KG260TN1D","Ferrite_Bead_Small","Capacitor_SMD:C_0603_1608Metric","Ferrite bead, small symbol",""
"J1, ","1","DEBUG","Conn_02x05_Odd_Even","Connector_Samtec_HLE_THT:Samtec_HLE-105-02-xx-DV-TE_2x05_P2.54mm_Horizontal","Generic connector, double row, 02x05, odd/even pin numbering scheme (row 1 odd numbers, row 2 even numbers), script generated (kicad-library-utils/schlib/autogen/connector/)",""
"J2, ","1","UART","Conn_01x04","Connector_PinSocket_2.54mm:PinSocket_1x04_P2.54mm_Vertical","Generic connector, single row, 01x04, script generated (kicad-library-utils/schlib/autogen/connector/)",""
"J3, ","1","USB","USB_C_Receptacle_USB2.0","Connector_USB:USB_C_Receptacle_HRO_TYPE-C-31-M-12","USB 2.0-only Type-C Receptacle connector",""
"J4, ","1","DISPLAY","Conn_01x04","Connector_PinSocket_2.54mm:PinSocket_1x04_P2.54mm_Vertical","Generic connector, single row, 01x04, script generated (kicad-library-utils/schlib/autogen/connector/)",""
"JP1, ","1","Jumper_NO_Small","Jumper_NO_Small","Jumper:SolderJumper-2_P1.3mm_Open_RoundedPad1.0x1.5mm","Jumper, normally open, small symbol",""
"JP2, ","1","BOOT0","SolderJumper_3_Open","Jumper:SolderJumper-3_P1.3mm_Open_RoundedPad1.0x1.5mm","Solder Jumper, 3-pole, open",""
"JP3, ","1","BOOT1","SolderJumper_3_Open","Jumper:SolderJumper-3_P1.3mm_Open_RoundedPad1.0x1.5mm","Solder Jumper, 3-pole, open",""
"R1, ","1","10K","R_Small","Resistor_SMD:R_0603_1608Metric","Resistor, small symbol",""
"R2, ","1","5K","R_Small","Resistor_SMD:R_0603_1608Metric","Resistor, small symbol",""
"R3, R14, ","2","10k","R_Small","Resistor_SMD:R_0603_1608Metric","Resistor, small symbol",""
"R4, R10, R11, R16, R18, R20, ","6","100K","R_Small","Resistor_SMD:R_0603_1608Metric","Resistor, small symbol",""
"R5, R6, ","2","20R","R_Small","Resistor_SMD:R_0603_1608Metric","Resistor, small symbol",""
"R7, R12, R13, ","3","4.7K","R_Small","Resistor_SMD:R_0603_1608Metric","Resistor, small symbol",""
"R8, R9, ","2","5.1K","R_Small","Resistor_SMD:R_0603_1608Metric","Resistor, small symbol",""
"R15, ","1","550R","R_Small","Resistor_SMD:R_0603_1608Metric","Resistor, small symbol",""
"R17, ","1","33K","R_Small","Resistor_SMD:R_0603_1608Metric","Resistor, small symbol",""
"R19, ","1","160R","R_Small","Resistor_SMD:R_0603_1608Metric","Resistor, small symbol",""
"R133, ","1","1M","R_Small","Resistor_SMD:R_0603_1608Metric","Resistor, small symbol",""
"S1, ","1","RESET","3-1437565-0","AA_Caliper:SW_3-1437565-0","",""
"S2, ","1","USER","3-1437565-0","AA_Caliper:SW_3-1437565-0","",""
"TP1, ","1","SIGNAL","TestPoint","TestPoint:TestPoint_Pad_D1.5mm","test point",""
"TP2, ","1","GND","TestPoint","TestPoint:TestPoint_Pad_D1.5mm","test point",""
"U1, ","1","GeneratorSensor","GeneratorSensor","AA_Caliper:excitation_electrodes","",""
"U2, ","1","MCP6S21-I_SN","MCP6S21-I_SN","AA_Caliper:SOIC127P600X175-8N","",""
"U3, ","1","TPS79333-EP","TPS79333-EP","Package_TO_SOT_SMD:SOT-23-5","200mA UltraLow-Noise, High-Precision, Fast RF, Low Drop-out Voltage Regualtor, Fixed Output 3.3V, SOT-23",""
"U4, ","1","STM32F103C8Tx","STM32F103C8Tx","Package_QFP:LQFP-48_7x7mm_P0.5mm","ARM Cortex-M3 MCU, 64KB flash, 20KB RAM, 72MHz, 2-3.6V, 37 GPIO, LQFP-48",""
"U5, ","1","ADR510ARTZ-REEL7","ADR510ARTZ-REEL7","AA_Caliper:SOT95P237X112-3N","",""
"U6, ","1","AD8603","AD8603","Package_TO_SOT_SMD:TSOT-23-5","Precision Micropower, Low Noise CMOS, Rail-to-Rail Input/Output Operational Amplifier, TSOT-23-5",""
"U9, ","1","32.7680KHz","Clock","AA_Caliper:XTAL_MC-306_32.7680K-A__ROHS","",""
"Y1, ","1","8MHz","Crystal","Crystal:Crystal_SMD_5032-2Pin_5.0x3.2mm","Two pin crystal",""

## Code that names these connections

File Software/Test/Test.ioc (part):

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Mcu.Name=STM32F103C(8-B)Tx
Mcu.Package=LQFP48
Mcu.UserName=STM32F103C8Tx
PA0-WKUP.Signal=GPIO_Output
PA1.Signal=GPIO_Output
PA10.Signal=GPIO_Output
PA11.Mode=Device
PA11.Signal=USB_DM
PA12.Mode=Device
PA12.Signal=USB_DP
PA13.Mode=Serial_Wire
PA13.Signal=SYS_JTMS-SWDIO
PA14.Mode=Serial_Wire
PA14.Signal=SYS_JTCK-SWCLK
PA2.Signal=GPIO_Output
PA3.Signal=GPIO_Output
PA4.Signal=GPIO_Output
PA5.Signal=GPIO_Output
PA6.Signal=GPIO_Output
PA7.Signal=GPIO_Output
PB1.Signal=ADCx_IN9
PB12.Mode=NSS_Signal_Hard_Output
PB12.Signal=SPI2_NSS
PB13.Mode=TX_Only_Simplex_Unidirect_Master
PB13.Signal=SPI2_SCK
PB14.GPIOParameters=GPIO_PuPd,GPIO_ModeDefaultEXTI
PB14.GPIO_ModeDefaultEXTI=GPIO_MODE_IT_FALLING
PB14.GPIO_PuPd=GPIO_PULLUP
PB14.Signal=GPXTI14
PB15.Mode=TX_Only_Simplex_Unidirect_Master
PB15.Signal=SPI2_MOSI
PC14-OSC32_IN.Mode=LSE-External-Oscillator
PC14-OSC32_IN.Signal=RCC_OSC32_IN
PC15-OSC32_OUT.Mode=LSE-External-Oscillator
PC15-OSC32_OUT.Signal=RCC_OSC32_OUT
PD0-OSC_IN.Mode=HSE-External-Oscillator
PD0-OSC_IN.Signal=RCC_OSC_IN
PD1-OSC_OUT.Mode=HSE-External-Oscillator
PD1-OSC_OUT.Signal=RCC_OSC_OUT
RCC.SYSCLKFreq_VALUE=72000000
RCC.SYSCLKSource=RCC_SYSCLKSOURCE_PLLCLK
board=custom

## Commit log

2024-02-10 Upload documents
2024-02-10 Create LICENSE
2024-02-10 upload gerbers, and more docks
2024-02-10 update footprints
2024-02-12 upload 3d models
2024-02-17 upload test program
2024-04-25 upload kicad project
2024-06-29 organize
2024-06-29 update docs
2024-07-20 sw update
2024-07-21 typo fix
2024-07-24 Initial arduino sketch
2024-07-24 updateforCubeMx
2024-07-27 swUpdate
2024-07-27 upload hex
2024-07-27 add oscilloscope
2024-09-15 update repo
2024-09-15 update blade step
2024-10-20 update source for new patterm
    update source for new patterm
2025-07-11 add simulation
2025-07-13 generate PDM
2026-01-22 added kicad project
